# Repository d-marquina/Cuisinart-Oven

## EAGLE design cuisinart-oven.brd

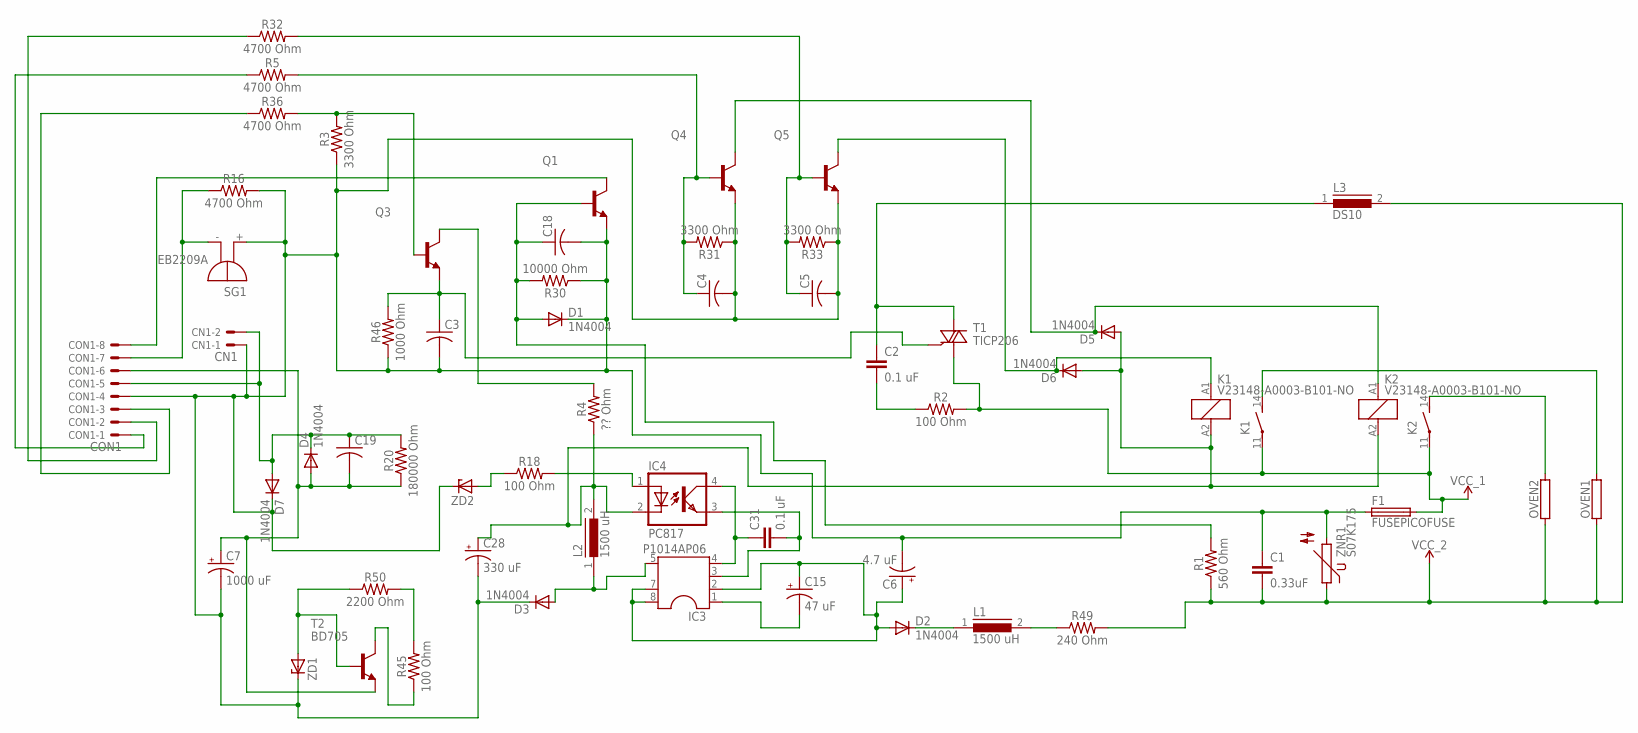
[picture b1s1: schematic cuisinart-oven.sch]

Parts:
C1: 0.33uF; C15B9
C2, C31: 0.1 uF; XC15B6
C3, C4, C5, C18, C19: C-US025-024X044; C025-024X044
C6: 4.7 uF; E3,5-8
C7: 1000 uF; E3,5-8
C15: 47 uF; E2-5
C28: 330 uF; E3,5-10
CN1: CN1; 22-23-2021
CON1: CON1; 22-23-2081
D1, D2, D3, D4, D5, D6, D7: 1N4004; DO41-10
F1: FUSEPICOFUSE; PICOFUSE
IC3: P1014AP06; DIP-8B
IC4: PC817; DIL04
K1, K2: V23148-A0003-B101-NO; V23148-NO
L1, L2: 1500 uH; 82114R
L3: DS10
OVEN1, OVEN2: RRWM10X65; RWM10X65
Q1, Q3, Q4, Q5: BFS17-NPN-SOT23-BEC; SOT23-BEC
R1: 560 Ohm; AXIAL-0.3
R2, R18, R45: 100 Ohm; AXIAL-0.3
R3, R31, R33: 3300 Ohm; AXIAL-0.3
R4: ?? Ohm; AXIAL-0.3
R5, R16, R32, R36: 4700 Ohm; AXIAL-0.3
R20: 180000 Ohm; AXIAL-0.3
R30: 10000 Ohm; AXIAL-0.3
R46: 1000 Ohm; AXIAL-0.3
R49: 240 Ohm; AXIAL-0.3
R50: 2200 Ohm; AXIAL-0.3
SG1: EB2209A
T1: TICP206; TO92-6
T2: BD705; TO220
ZD1, ZD2: ZENER_DIODEDO41Z10; DO41Z10
ZNR1: S07K175

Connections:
unnamed: L1.2, R49.P$1 (1)
unnamed: C2.2, R2.P$1 (1)
unnamed: C28.+, D5.A, D6.A, IC4.2 (C), K1.A2 (2), K2.A2 (2), L2.2, R4.P$1 (1)
unnamed: K2.14 (S), OVEN2.2
unnamed: K1.14 (S), OVEN1.2
unnamed: D5.C, K2.A1 (1), Q4.C
unnamed: D2.C, L1.1
unnamed: D6.C, K1.A1 (1), Q5.C
unnamed: C6.+, C15.+, D2.A, IC3.2 (2GND), IC3.7 (7HV-GND), IC3.8 (8HV-GND)
unnamed: CON1.3, R36.P$1 (1)
unnamed: C15.-, IC3.1 (BP)
unnamed: C2.1, L3.1, T1.A2
unnamed: C31.2, IC3.3 (3GND), IC4.3 (EMIT)
unnamed: C1.1, C3.2, C4.2, C5.2, C6.-, C7.-, C18.2, C28.-, CN1.1, CON1.4, D1.C, D3.C, D7.C, F1.1, Q1.E, Q4.E, Q5.E, R3.P$1 (1), R16.P$2 (2), R30.P$1 (1), R31.P$1 (1), R33.P$1 (1), R46.P$1 (1), SG1.+, ZD1.C (CATHODE), ZD2.C (CATHODE), ZNR1.2
unnamed: C31.1, IC3.4 (EN/UV), IC4.4 (COL)
unnamed: IC4.1 (A), R18.P$2 (2)
unnamed: D3.A, IC3.5 (D), L2.1
unnamed: R18.P$1 (1), ZD2.A (ANODE)
unnamed: C18.1, D1.A, Q1.B, R1.P$2 (2), R30.P$2 (2)
unnamed: CON1.7, R16.P$1 (1), SG1.-
unnamed: R45.P$1 (1), T2.2 (C)
unnamed: R45.P$2 (2), R50.P$2 (2)
unnamed: R50.P$1 (1), T2.1 (B), ZD1.A (ANODE)
unnamed: C19.1, CN1.2, CON1.5, D4.C, D7.A, R20.P$2 (2)
unnamed: Q3.B, R3.P$2 (2), R36.P$2 (2)
unnamed: Q3.C, R4.P$2 (2)
unnamed: C3.1, Q3.E, R46.P$2 (2), T1.G
unnamed: CON1.8, Q1.C
unnamed: C5.1, Q5.B, R32.P$2 (2), R33.P$2 (2)
unnamed: C7.+, C19.2, CON1.6, D4.A, R20.P$1 (1), T2.3 (E)
unnamed: C4.1, Q4.B, R5.P$2 (2), R31.P$2 (2)
unnamed: CON1.2, R32.P$1 (1)
unnamed: CON1.1, R5.P$1 (1)
VCC_1: F1.2, K1.11, K2.11, R2.P$2 (2), T1.A1
VCC_2: C1.2, L3.2, OVEN1.1, OVEN2.1, R1.P$1 (1), R49.P$2 (2), ZNR1.1

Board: 2 copper layers, 58 parts (0 on the bottom side), 35 nets, no tracks yet.

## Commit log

2018-02-27 Complete schematic
    Finally the circuit is complete.

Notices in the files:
parts and their libraries:
SparkFun-Resistors: Licensing: Creative Commons ShareAlike 4.0 International - https://creativecommons.org/licenses/by-sa/4.0
